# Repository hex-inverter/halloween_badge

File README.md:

# haloween_badge

This project is currently WIP!

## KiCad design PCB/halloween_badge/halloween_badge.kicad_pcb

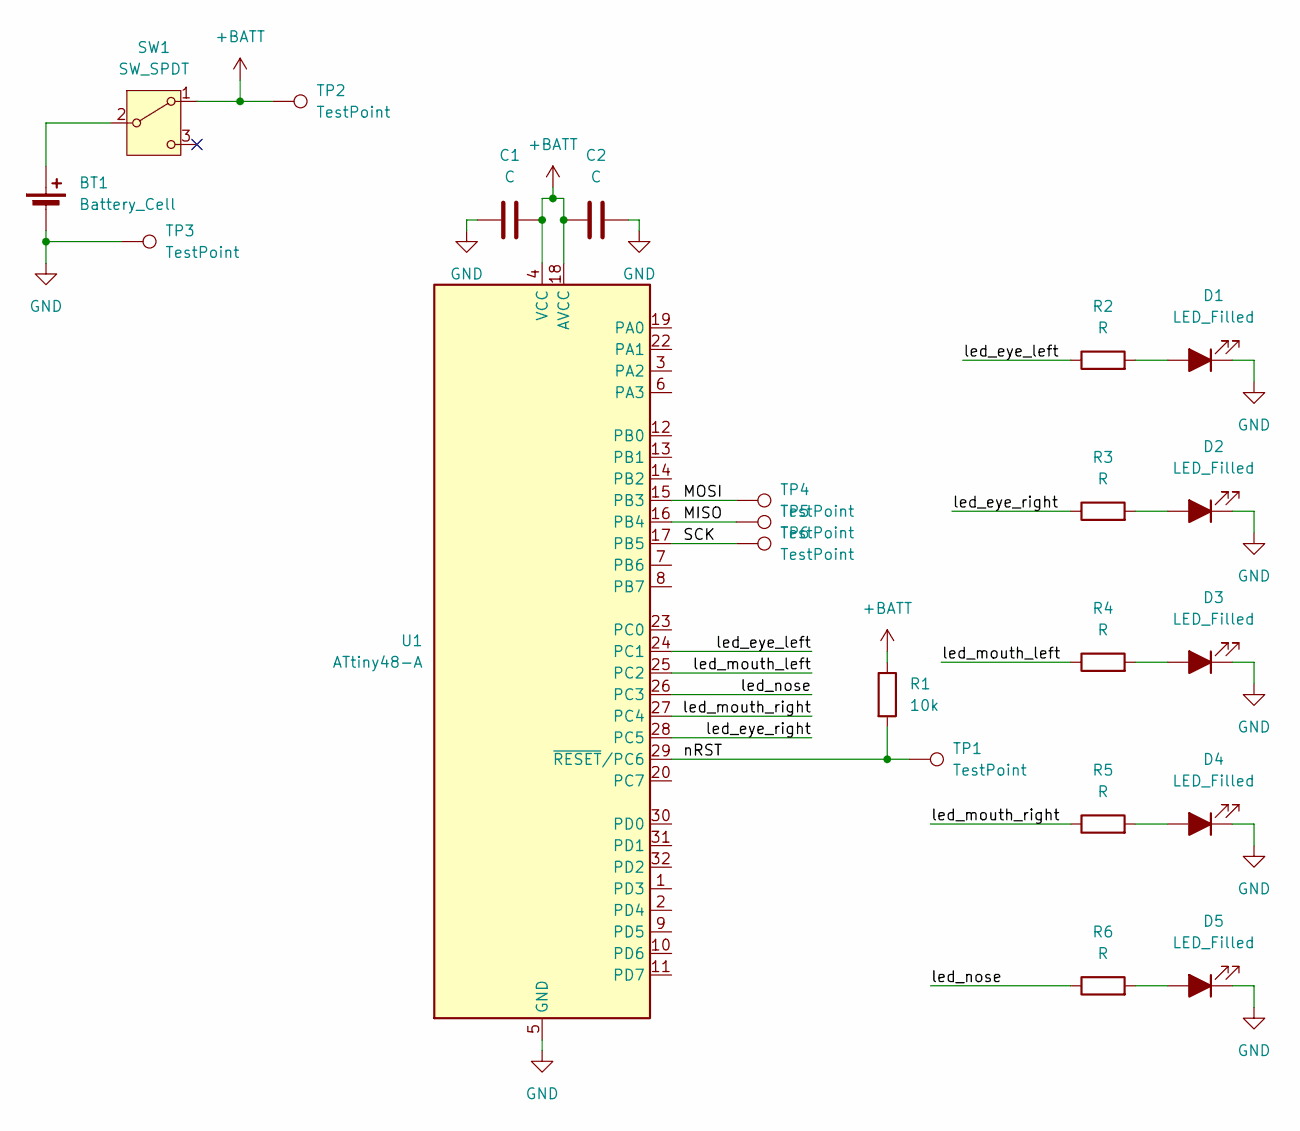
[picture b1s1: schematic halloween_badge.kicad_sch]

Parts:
BT1: Battery_Cell; PinHeader_2x01_P2.54mm_Vertical_SMD
C1, C2: C; C_0402_1005Metric_Pad0.74x0.62mm_HandSolder
D1, D2, D3, D4, D5: LED_Filled; LED_0603_1608Metric_Pad1.05x0.95mm_HandSolder
R1: 10k; R_0402_1005Metric_Pad0.72x0.64mm_HandSolder
R2, R3, R4, R5, R6: R; R_0402_1005Metric_Pad0.72x0.64mm_HandSolder
SW1: SW_SPDT; SW_SPDT_CK_JS102011SAQN
TP1, TP2, TP3, TP4, TP5, TP6: TestPoint; TestPoint_Pad_1.5x1.5mm
U1: ATtiny48-A; TQFP-32_7x7mm_P0.8mm

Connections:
+BATT: C1.2, C2.1, R1.1, SW1.1 (A), TP2.1, U1.4 (VCC), U1.18 (AVCC)
/MISO: TP5.1, U1.16 (PB4)
/MOSI: TP4.1, U1.15 (PB3)
/SCK: TP6.1, U1.17 (PB5)
/led_eye_left: R2.1, U1.24 (PC1)
/led_eye_right: R3.1, U1.28 (PC5)
/led_mouth_left: R4.1, U1.25 (PC2)
/led_mouth_right: R5.1, U1.27 (PC4)
/led_nose: R6.1, U1.26 (PC3)
/nRST: R1.2, TP1.1, U1.29 (~RESET/PC6)
GND: BT1.2 (-), C1.1, C2.2, D1.1 (K), D2.1 (K), D3.1 (K), D4.1 (K), D5.1 (K), TP3.1, U1.5 (GND), U1.21 (GND)
unnamed: BT1.1 (+), SW1.2 (B)
unnamed: D1.2 (A), R2.2
unnamed: D2.2 (A), R3.2
unnamed: D3.2 (A), R4.2
unnamed: D4.2 (A), R5.2
unnamed: D5.2 (A), R6.2

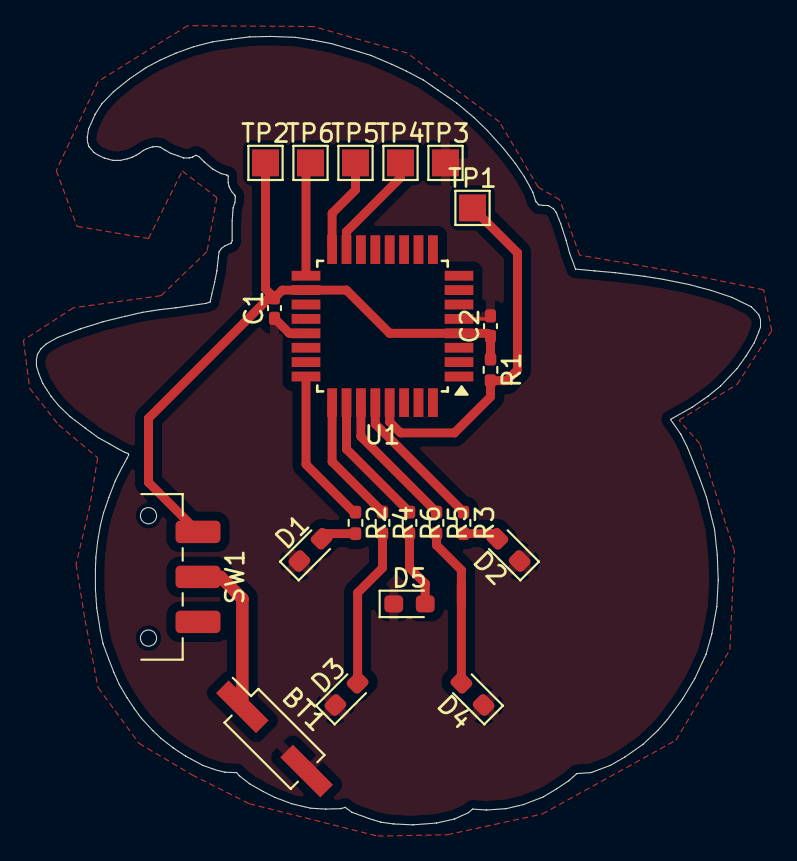
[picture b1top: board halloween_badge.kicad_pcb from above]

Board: 2 copper layers, 40.2 x 43.8 mm, 22 parts (0 on the bottom side), 17 nets.

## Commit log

2024-10-28 partial PCB concept design
2024-10-29 first finished PCB design
2024-10-29 increased width of traces, added graphics
2024-10-30 Added firmware
